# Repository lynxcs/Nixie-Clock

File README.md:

<p align="center">

  <h1 align="center"><b>Nixie Clock</b></h1>

  <p align="center">
    Nixie clock for my design class, including the 3D renders, PCB design and photos of the finished pcb.
  </p>

<p align="center">
  
  </p>
</p>

<!-- ABOUT THE PROJECT -->
# About The Project
<a href="https://github.com/lynxcs/Nixie-Clock/blob/master/aprasymas.pdf">Details in lithuanian here</a>

## Tools used
<p>
    The nixie clock was made using Blender, inkscape and kicad.
</p>

## 3D Model
<p>First the 3D render was created as a rough idea about how I wanted the clock to look</p>

## Case design
<p> Afterward I designed a blueprint with the dimensions for the case design </p>

## Schematic
<p> Upon completion of the case design, I started to work on the schematic </p>

## Components
<p>
    The PCB makes use of several components. The key components have been listed below
    <ul>
    <li>Arduino Pro Mini</li>
    <li>IN-4 Nixie Digits</li>
    <li>INS-1 Nixie Indicators</li>
    <li>K155ID1 high voltage drivers</li>
    <li>NCH8200HV high voltage boost converter (5v to 170v)</li>
    </ul>
</p>

## PCB Layout
<p> Then I made the PCB layout, trying my best to make it as small as possible, though sadly it wouldn't fit in the original case design dimensions</p>

## Assembly
<p> Lastly I ordered the PCB's and got to soldering and programming</p>

## Case mounting
<p><i>This part is still W.I.P</i></p>

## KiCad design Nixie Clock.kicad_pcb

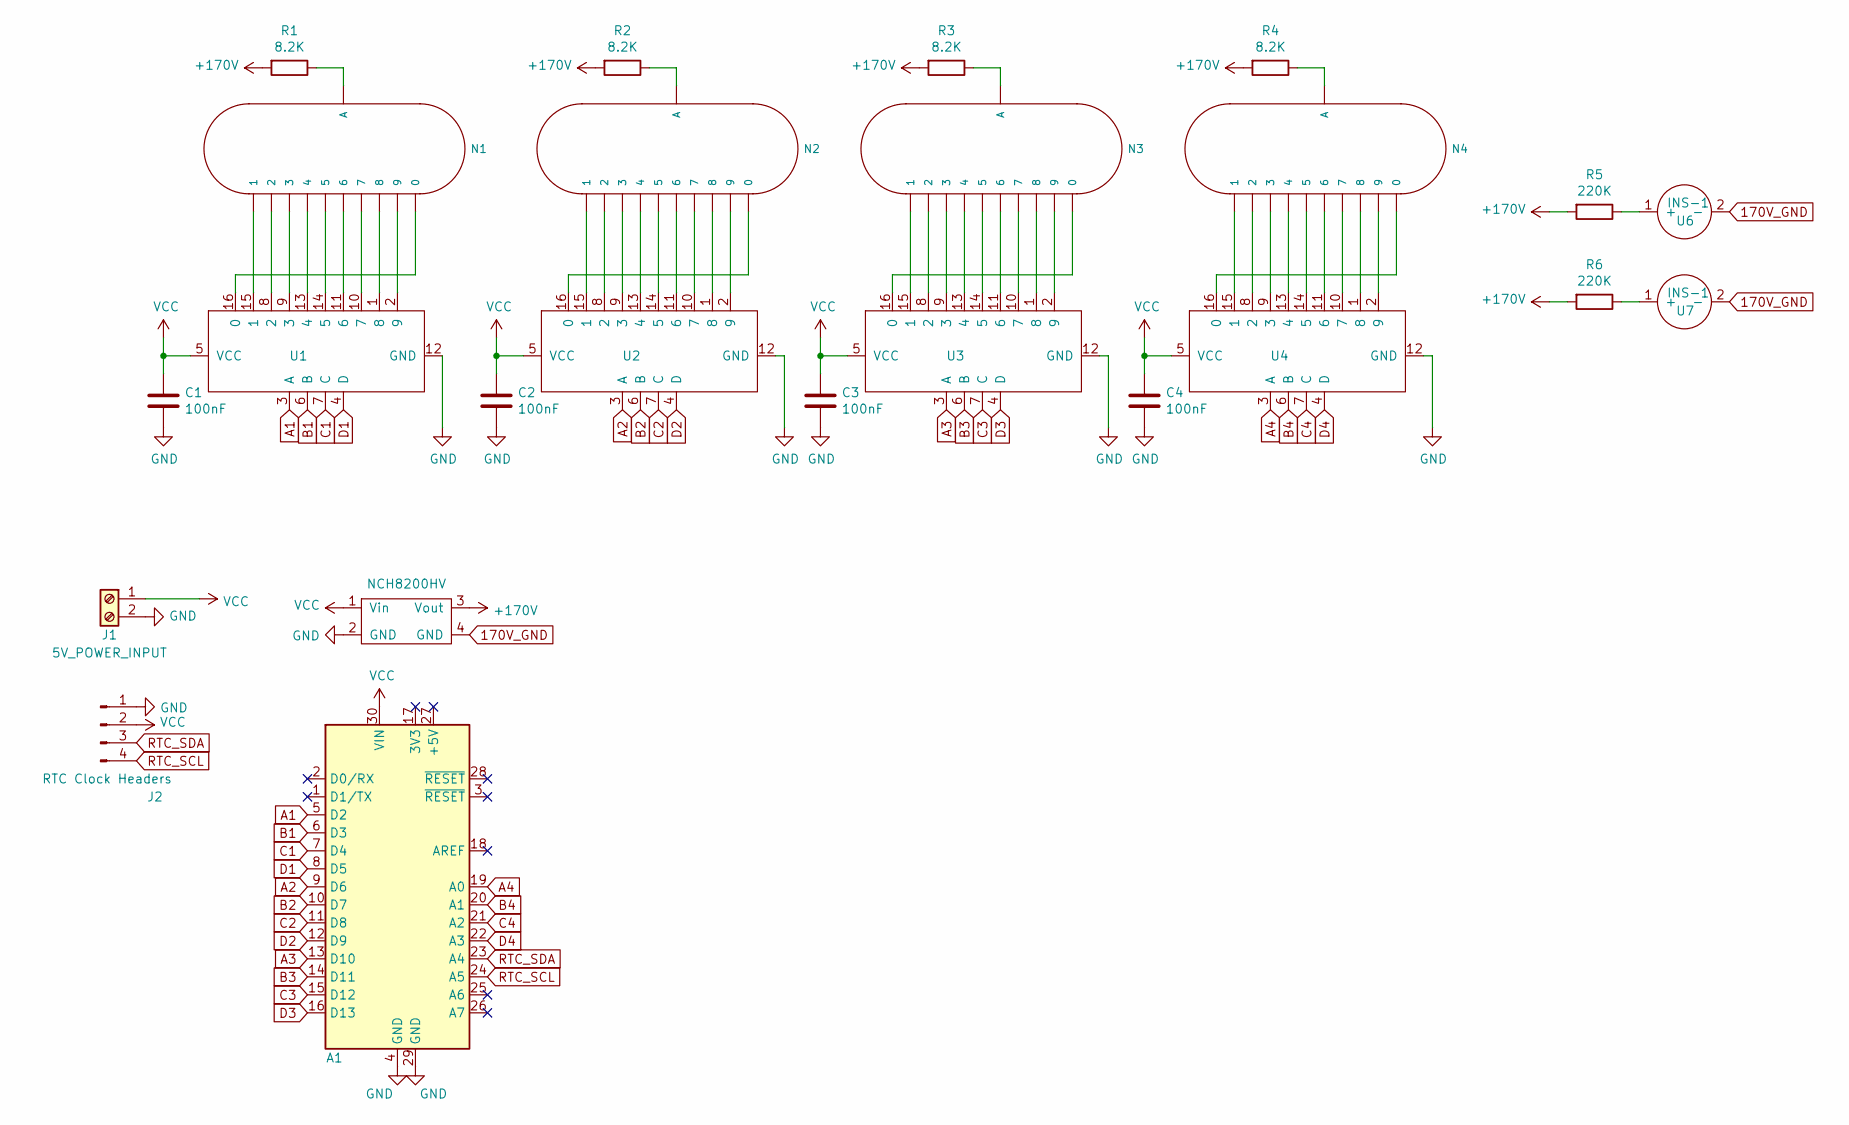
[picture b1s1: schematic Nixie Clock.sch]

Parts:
A1: Arduino_Nano_v3.x; Arduino_Nano
C1, C2, C3, C4: 100nF; C_0603_1608Metric; LCSC C15725
J1: 5V_POWER_INPUT; PinHeader_1x02_P2.54mm_Vertical
J2: RTC Clock Headers; PinHeader_1x04_P2.54mm_Vertical
N1, N2, N3, N4: IN-4; nixies-us-IN-4-DSUB
R1, R2, R3, R4: 8.2K; R_0603_1608Metric; LCSC C25981
R5, R6: 220K; R_0603_1608Metric; LCSC C22961
U1, U2, U3, U4: K155ID1
U5: NCH8200HV
U6, U7: INS-1

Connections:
170V_GND: U5.4 (GND), U6.2 (-), U7.2 (-)
+170V: R1.2, R2.2, R3.2, R4.2, R5.2, R6.2, U5.3 (Vout)
A1: A1.5 (D2), U1.3 (A)
A2: A1.9 (D6), U2.3 (A)
A3: A1.13 (D10), U3.3 (A)
A4: A1.19 (A0), U4.3 (A)
B1: A1.6 (D3), U1.6 (B)
B2: A1.10 (D7), U2.6 (B)
B3: A1.14 (D11), U3.6 (B)
B4: A1.20 (A1), U4.6 (B)
C1: A1.7 (D4), U1.7 (C)
C2: A1.11 (D8), U2.7 (C)
C3: A1.15 (D12), U3.7 (C)
C4: A1.21 (A2), U4.7 (C)
D1: A1.8 (D5), U1.4 (D)
D2: A1.12 (D9), U2.4 (D)
D3: A1.16 (D13), U3.4 (D)
D4: A1.22 (A3), U4.4 (D)
GND: A1.4 (GND), A1.29 (GND), C1.2, C2.2, C3.2, C4.2, J1.2, J2.1, U1.12 (GND), U2.12 (GND), U3.12 (GND), U4.12 (GND), U5.2 (GND)
unnamed: N1.0, U1.16 (0)
unnamed: N1.1, U1.15 (1)
unnamed: N1.2, U1.8 (2)
unnamed: N1.3, U1.9 (3)
unnamed: N1.4, U1.13 (4)
unnamed: N1.5, U1.14 (5)
unnamed: N1.6, U1.11 (6)
unnamed: N1.7, U1.10 (7)
unnamed: N1.8, U1.1 (8)
unnamed: N1.9, U1.2 (9)
unnamed: N1.A3 (A), R1.1
unnamed: N2.0, U2.16 (0)
unnamed: N2.1, U2.15 (1)
unnamed: N2.2, U2.8 (2)
unnamed: N2.3, U2.9 (3)
unnamed: N2.4, U2.13 (4)
unnamed: N2.5, U2.14 (5)
unnamed: N2.6, U2.11 (6)
unnamed: N2.7, U2.10 (7)
unnamed: N2.8, U2.1 (8)
unnamed: N2.9, U2.2 (9)
unnamed: N2.A3 (A), R2.1
unnamed: N3.0, U3.16 (0)
unnamed: N3.1, U3.15 (1)
unnamed: N3.2, U3.8 (2)
unnamed: N3.3, U3.9 (3)
unnamed: N3.4, U3.13 (4)
unnamed: N3.5, U3.14 (5)
unnamed: N3.6, U3.11 (6)
unnamed: N3.7, U3.10 (7)
unnamed: N3.8, U3.1 (8)
unnamed: N3.9, U3.2 (9)
unnamed: N3.A3 (A), R3.1
unnamed: N4.0, U4.16 (0)
unnamed: N4.1, U4.15 (1)
unnamed: N4.2, U4.8 (2)
unnamed: N4.3, U4.9 (3)
unnamed: N4.4, U4.13 (4)
unnamed: N4.5, U4.14 (5)
unnamed: N4.6, U4.11 (6)
unnamed: N4.7, U4.10 (7)
unnamed: N4.8, U4.1 (8)
unnamed: N4.9, U4.2 (9)
unnamed: N4.A3 (A), R4.1
unnamed: R5.1, U6.1 (+)
unnamed: R6.1, U7.1 (+)
RTC_SCL: A1.24 (A5), J2.4
RTC_SDA: A1.23 (A4), J2.3
VCC: A1.30 (VIN), C1.1, C2.1, C3.1, C4.1, J1.1, J2.2, U1.5 (VCC), U2.5 (VCC), U3.5 (VCC), U4.5 (VCC), U5.1 (Vin)

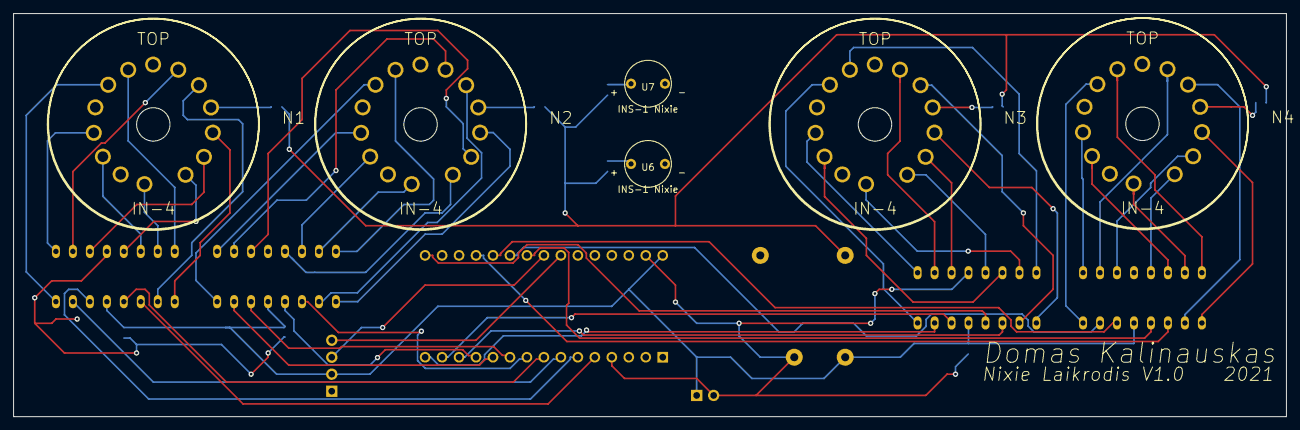
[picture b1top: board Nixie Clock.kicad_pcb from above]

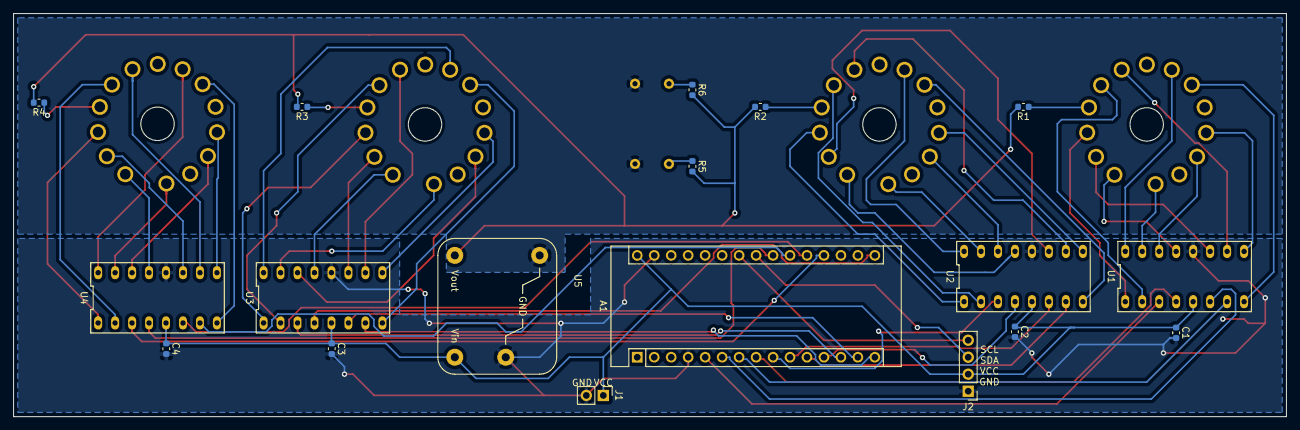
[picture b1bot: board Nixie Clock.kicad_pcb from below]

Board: 2 copper layers, 190.5 x 60.3 mm, 24 parts (18 on the bottom side), 68 nets.

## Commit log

2021-08-10 Fix link in README.md
2021-11-11 Create LICENSE
